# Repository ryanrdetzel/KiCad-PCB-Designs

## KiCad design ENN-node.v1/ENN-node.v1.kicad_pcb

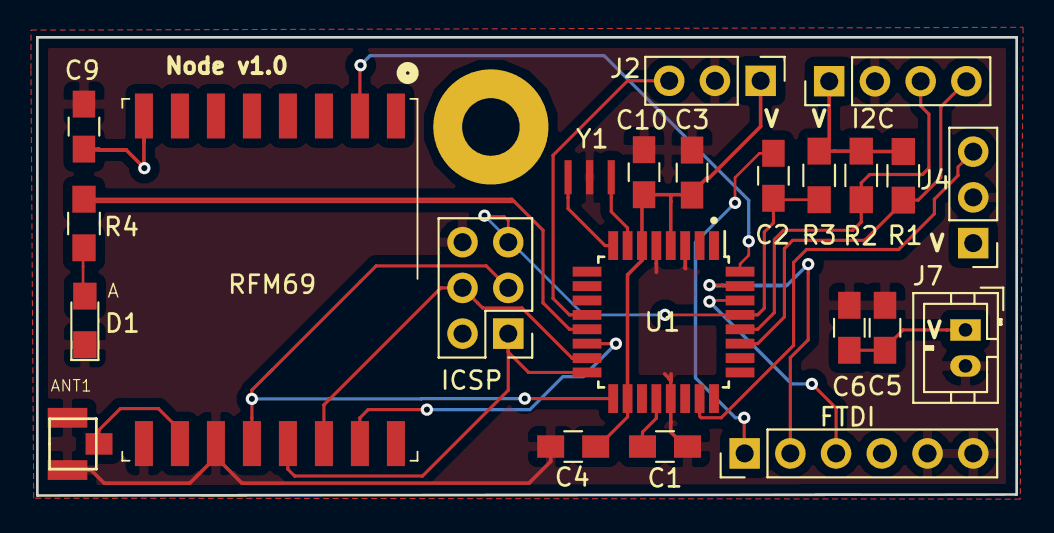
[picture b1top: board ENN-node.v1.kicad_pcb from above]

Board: 2 copper layers, 54.4 x 25.5 mm, 23 parts (0 on the bottom side), 21 nets.

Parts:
ANT1: Conn_Coaxial; CONN-RF-UFL
C1, C2: 0.1uF; C_0805_HandSoldering
C3, C4, C5, C9, C10: 0.1uf; C_0805_HandSoldering
C6: 10uf; C_0805_HandSoldering
D1: LED; LED_0805_HandSoldering
FTDI: FTDI; Pin_Header_Straight_1x06_Pitch2.54mm
I2C: I2C Bus; Pin_Header_Straight_1x04_Pitch2.54mm
ICSP: ICSP; Pin_Header_Straight_2x03_Pitch2.54mm
J2: Digital Connector; Pin_Header_Straight_1x03_Pitch2.54mm
J4: Analog Connector; Pin_Header_Straight_1x03_Pitch2.54mm
J7: Power Connector; JST_PH_B2B-PH-K_02x2.00mm_Straight
R1, R2: 4k7; R_0805_HandSoldering
R3: 10k; R_0805_HandSoldering
R4: 330; R_0805_HandSoldering
RFM69: RFM69W; HOPERF-RFM69HW
U1: ATmega328P-AU; TQFP-32_7x7mm_Pitch0.8mm
Y1: Resonator; ResTest

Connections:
/A0: J4.3, U1.23
/D2: RFM69.2, U1.32
/D8: J2.3, U1.12
/D9: R4.2, U1.13
/DTR: C2.2, FTDI.1
/MISO: ICSP.1, RFM69.13, U1.16
/MOSI: ICSP.4, RFM69.14, U1.15
/RST: C2.1, ICSP.5, R3.2, U1.29
/RX: FTDI.3, U1.30
/SCK: ICSP.3, RFM69.12, U1.17
/SCL: I2C.3, R2.1, U1.28
/SDA: I2C.4, R1.1, U1.27
/SS: RFM69.15, U1.14
/TX: FTDI.2, U1.31
/VCC: C3.1, C4.1, C5.1, C6.1, C9.2, C10.1, FTDI.4, I2C.1, ICSP.2, J2.1, J4.1, J7.1, R1.2, R2.2, R3.1, RFM69.8, U1.4, U1.6, U1.18
GND: ANT1.2, C1.1, C3.2, C4.2, C5.2, C6.2, C9.1, C10.2, D1.1, FTDI.5, FTDI.6, I2C.2, ICSP.6, J2.2, J4.2, J7.2, RFM69.9, RFM69.11, U1.3, U1.5, U1.21, Y1.2
unnamed: ANT1.1, RFM69.10
unnamed: C1.2, U1.20
unnamed: D1.2, R4.1
unnamed: U1.7, Y1.3
unnamed: U1.8, Y1.1

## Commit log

2019-03-17 wireless rfm69 node
